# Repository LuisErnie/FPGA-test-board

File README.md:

# FPGA-test-board
FPGA Test Board designed for use with **DE10-NANO** by Terasic to provide external I/O devices to interface with the FPGA:
- 40 pin GPIO header split into 5 PMod ports
- 16x2 Character LCD
- 2 UART RS-485 ports
- 1 UART RS-282/USB port selected with switch
- 8 Optocoupled Outputs
- 8 ADC inputs 12-bit
- 8 DIP switch input

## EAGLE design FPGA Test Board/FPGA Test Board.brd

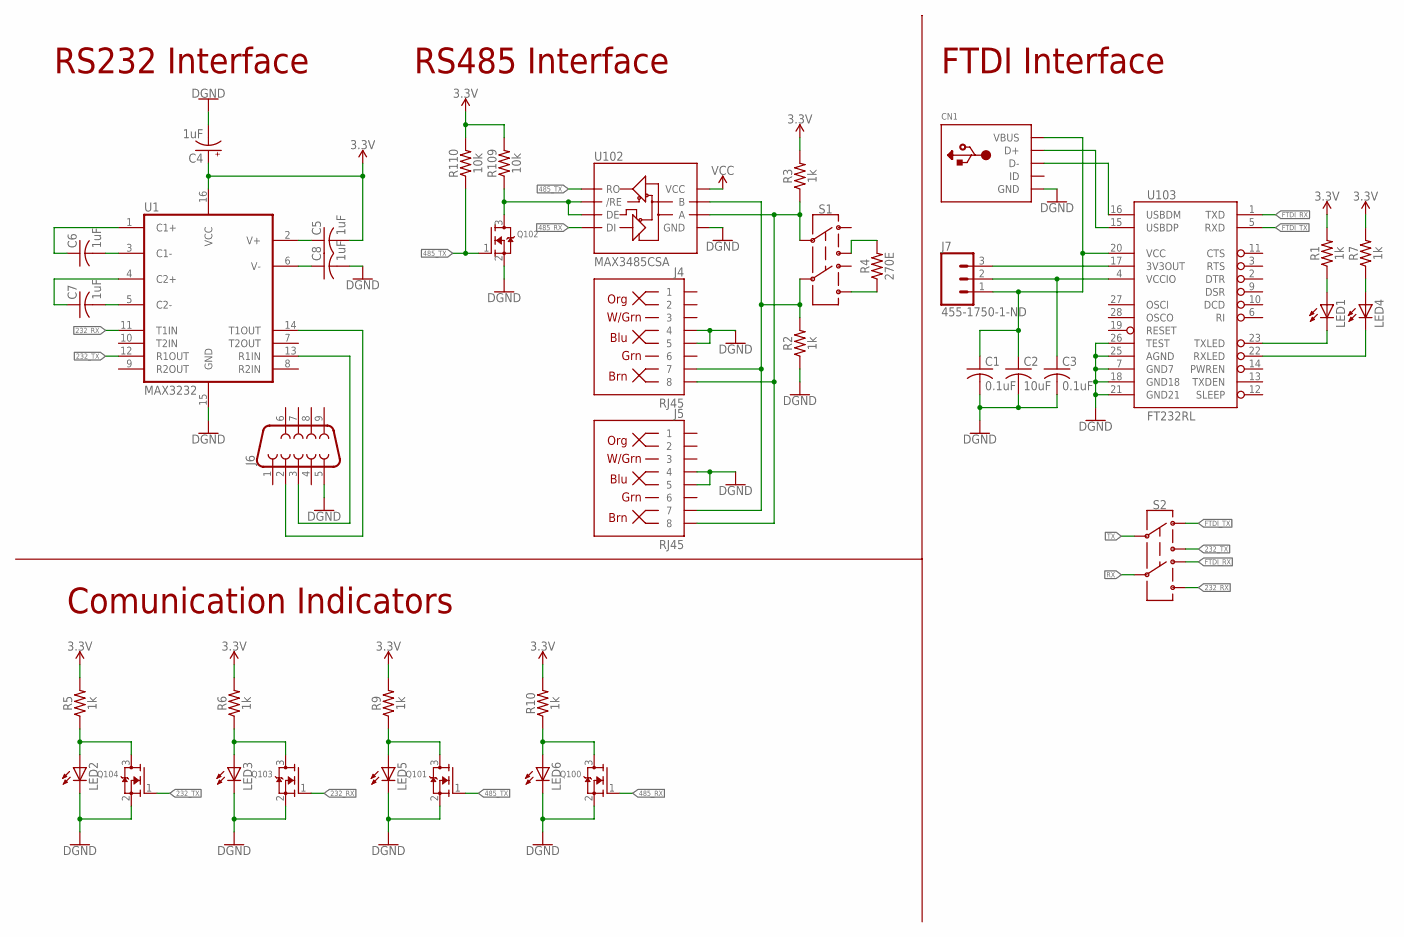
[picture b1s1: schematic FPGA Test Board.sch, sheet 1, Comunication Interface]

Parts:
C1, C3: 0.1uF; C0805
C2: 10uF; C0805
C4: 1uF; PANASONIC_B
C5, C6, C7, C8: 1uF; C0805
CN1: USBMINIB; USB-MINIB
J4, J5: RJ45; RJ45-8
J6: DB9FEMALE; DB9
J7: 455-1750-1-ND; 1X03
LED1, LED2, LED3, LED4, LED5, LED6: LEDCHIP-LED0805; CHIP-LED0805
Q100, Q101, Q102, Q103, Q104: MOSFET-NWAVE; SOT23-W
R1, R2, R3, R5, R6, R7, R9, R10: 1k; 0805
R4: 270E; 0805
R109, R110: 10k; 0805
S1, S2: SWITCH-DPDT-SMD-AYZ0202; SWITCH_DPDT_SMD_AYZ0202
U1: MAX3232; SO16
U102: MAX3485CSA; SO08
U103: FT232RL; SSOP28DB

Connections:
3.3V: C4.+, C5.2, R1.2, R3.2, R5.2, R6.2, R7.2, R9.2, R10.2, R109.2, R110.2, U1.16 (VCC); also elsewhere on the board
5V: U102.8 (VCC); also elsewhere on the board
232_RX: Q103.1 (G), S2.6, U1.11 (T1IN); also elsewhere on the board
232_TX: Q104.1 (G), S2.3, U1.12 (R1OUT); also elsewhere on the board
485_RX: Q100.1 (G), U102.4 (DI); also elsewhere on the board
485_TX: Q101.1 (G), Q102.1 (G), R110.1, U102.1 (RO); also elsewhere on the board
FTDI_RX: S2.4, U103.1 (TXD)
FTDI_TX: S2.1, U103.5 (RXD)
GND: C1.2, C2.2, C3.2, C4.-, C8.2, CN1.GND, J4.4, J4.5, J5.4, J5.5, J6.5, LED2.C, LED3.C, LED5.C, LED6.C, Q100.2 (S), Q101.2 (S), Q102.2 (S), Q103.2 (S), Q104.2 (S), R2.1, U1.15 (GND), U102.5 (GND), U103.7 (GND7), U103.18 (GND18), U103.21 (GND21), U103.25 (AGND), U103.26 (TEST); also elsewhere on the board
unnamed: C6.2, U1.3 (C1-)
unnamed: C5.1, U1.2 (V+)
unnamed: C6.1, U1.1 (C1+)
unnamed: C7.1, U1.4 (C2+)
unnamed: C7.2, U1.5 (C2-)
unnamed: C8.1, U1.6 (V-)
unnamed: J4.8, J5.8, R3.1, S1.2, U102.6 (A)
unnamed: LED3.A, Q103.3 (D), R6.1
unnamed: J6.2, U1.14 (T1OUT)
unnamed: J6.3, U1.13 (R1IN)
unnamed: LED5.A, Q101.3 (D), R9.1
unnamed: LED2.A, Q104.3 (D), R5.1
unnamed: LED6.A, Q100.3 (D), R10.1
unnamed: J4.7, J5.7, R2.2, S1.5, U102.7 (B)
unnamed: R4.1, S1.6
unnamed: Q102.3 (D), R109.1, U102.2 (/RE), U102.3 (DE)
unnamed: R4.2, S1.3
unnamed: C1.1, C2.1, CN1.VBUS, J7.1, U103.20 (VCC)
unnamed: LED1.A, R1.1
unnamed: LED1.C, U103.23 (TXLED)
unnamed: LED4.A, R7.1
unnamed: LED4.C, U103.22 (RXLED)
unnamed: CN1.D-, U103.16 (USBDM)
unnamed: CN1.D+, U103.15 (USBDP)
unnamed: J7.3, U103.17 (3V3OUT)
unnamed: C3.1, J7.2, U103.4 (VCCIO)
RX: S2.5
TX: S2.2

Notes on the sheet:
RS232 Interface
RS485 Interface
Comunication Indicators
FTDI Interface

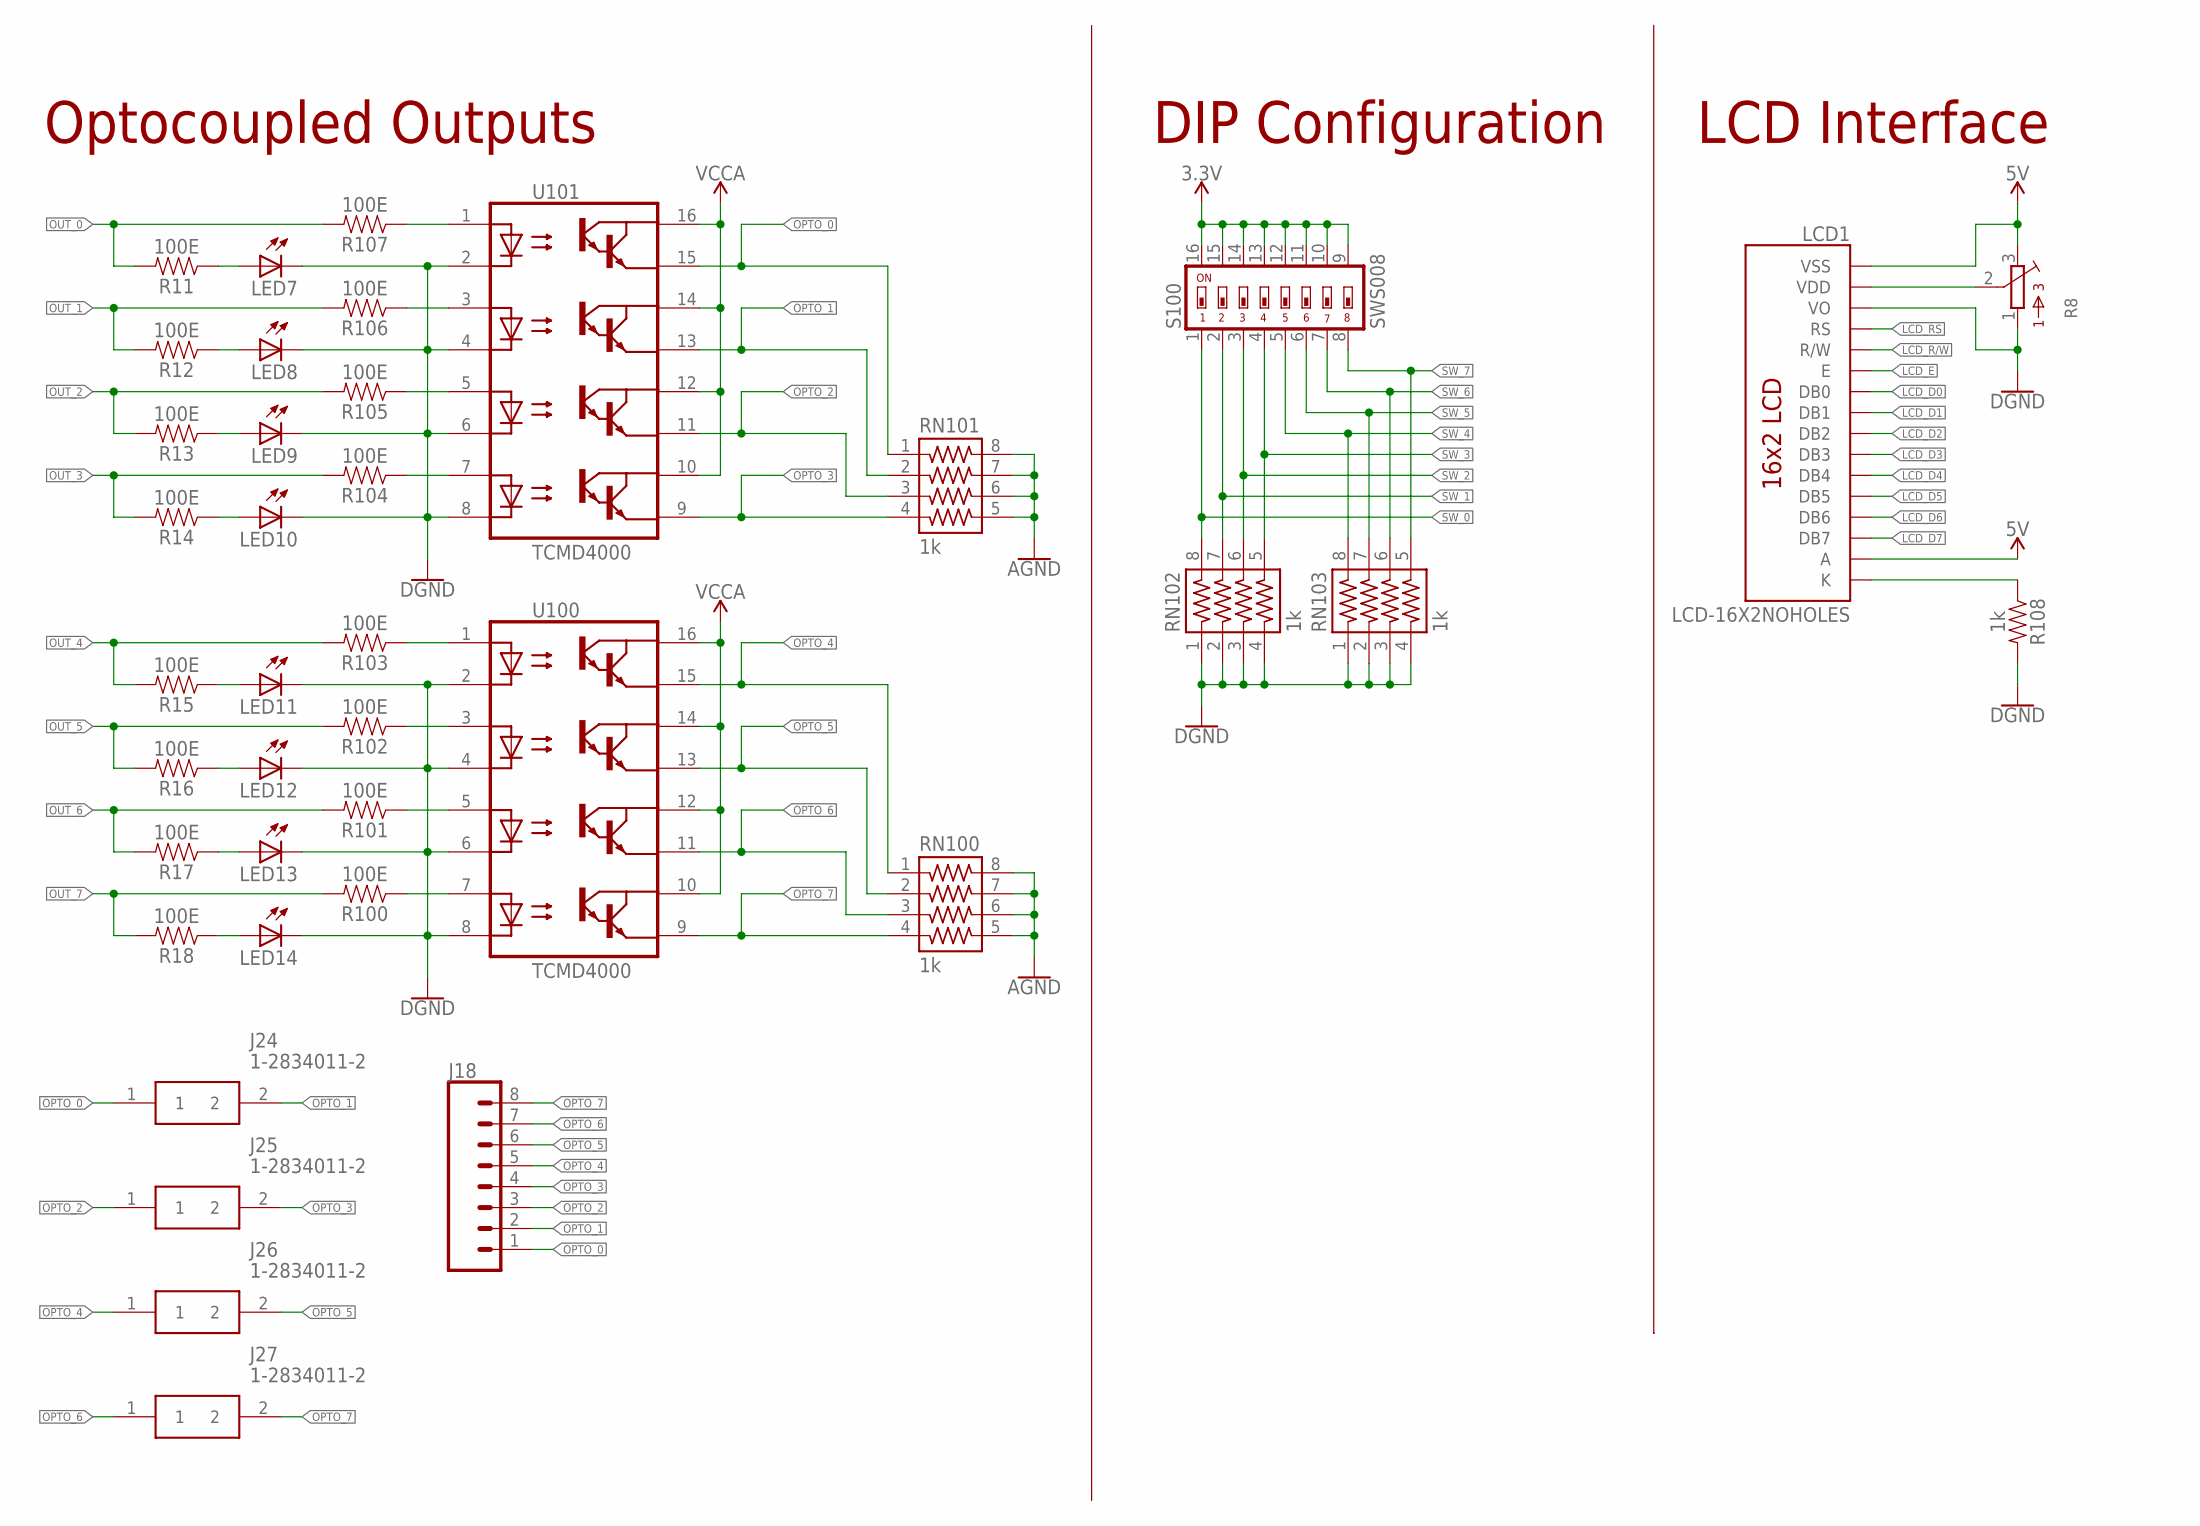
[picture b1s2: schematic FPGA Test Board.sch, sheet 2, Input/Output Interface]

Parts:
J18: CONN_08FEMALE_LOCK; 1X08_FEMALE_LOCK
J24, J25, J26, J27: 1-2834011-2; 128340112
LCD1: LCD-16X2NOHOLES; LCD-16X2_NOHOLESNOSILK
LED7, LED8, LED9, LED10, LED11, LED12, LED13, LED14: LEDCHIP-LED0805; CHIP-LED0805
R8: 3386-P; 3386P
R11, R12, R13, R14, R15, R16, R17, R18, R100, R101, R102, R103, R104, R105, R106, R107: 100E; 0805
R108: 1k; 0805
RN100, RN101, RN102, RN103: 1k; 743-8NS
S100: SWS008; SMS-008
U100, U101: TCMD4000; SOIC127P686X201-16N

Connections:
3.3V: S100.9, S100.10, S100.11, S100.12, S100.13, S100.14, S100.15, S100.16; also elsewhere on the board
5V: LCD1.1 (VSS), LCD1.15 (A), R8.3; also elsewhere on the board
AGND: RN100.5, RN100.6, RN100.7, RN100.8, RN101.5, RN101.6, RN101.7, RN101.8; also elsewhere on the board
GND: LCD1.3 (VO), LED7.C, LED8.C, LED9.C, LED10.C, LED11.C, LED12.C, LED13.C, LED14.C, R8.1, R108.2, RN102.1, RN102.2, RN102.3, RN102.4, RN103.1, RN103.2, RN103.3, RN103.4, U100.2 (C1), U100.4 (C2), U100.6 (C3), U100.8 (C4), U101.2 (C1), U101.4 (C2), U101.6 (C3), U101.8 (C4); also elsewhere on the board
LCD_D0: LCD1.7 (DB0); also elsewhere on the board
LCD_D1: LCD1.8 (DB1); also elsewhere on the board
LCD_D2: LCD1.9 (DB2); also elsewhere on the board
LCD_D3: LCD1.10 (DB3); also elsewhere on the board
LCD_D4: LCD1.11 (DB4); also elsewhere on the board
LCD_D5: LCD1.12 (DB5); also elsewhere on the board
LCD_D6: LCD1.13 (DB6); also elsewhere on the board
LCD_D7: LCD1.14 (DB7); also elsewhere on the board
LCD_E: LCD1.6 (E); also elsewhere on the board
LCD_R/W: LCD1.5 (R/W); also elsewhere on the board
LCD_RS: LCD1.4 (RS); also elsewhere on the board
unnamed: LCD1.2 (VDD), R8.2
unnamed: LCD1.16 (K), R108.1
unnamed: R107.1, U101.1 (A1)
unnamed: R106.1, U101.3 (A2)
unnamed: R105.1, U101.5 (A3)
unnamed: R104.1, U101.7 (A4)
unnamed: LED10.A, R14.1
unnamed: LED9.A, R13.1
unnamed: LED8.A, R12.1
unnamed: LED7.A, R11.1
unnamed: R103.1, U100.1 (A1)
unnamed: R102.1, U100.3 (A2)
unnamed: R101.1, U100.5 (A3)
unnamed: R100.1, U100.7 (A4)
unnamed: LED14.A, R18.1
unnamed: LED13.A, R17.1
unnamed: LED12.A, R16.1
unnamed: LED11.A, R15.1
OPTO_0: J18.1, J24.1, RN101.1, U101.15 (E1)
OPTO_1: J18.2, J24.2, RN101.2, U101.13 (E2)
OPTO_2: J18.3, J25.1, RN101.3, U101.11 (E3)
OPTO_3: J18.4, J25.2, RN101.4, U101.9 (E4)
OPTO_4: J18.5, J26.1, RN100.1, U100.15 (E1)
OPTO_5: J18.6, J26.2, RN100.2, U100.13 (E2)
OPTO_6: J18.7, J27.1, RN100.3, U100.11 (E3)
OPTO_7: J18.8, J27.2, RN100.4, U100.9 (E4)
OUT_0: R11.2, R107.2; also elsewhere on the board
OUT_1: R12.2, R106.2; also elsewhere on the board
OUT_2: R13.2, R105.2; also elsewhere on the board
OUT_3: R14.2, R104.2; also elsewhere on the board
OUT_4: R15.2, R103.2; also elsewhere on the board
OUT_5: R16.2, R102.2; also elsewhere on the board
OUT_6: R17.2, R101.2; also elsewhere on the board
OUT_7: R18.2, R100.2; also elsewhere on the board
SW_0: RN102.8, S100.1; also elsewhere on the board
SW_1: RN102.7, S100.2; also elsewhere on the board
SW_2: RN102.6, S100.3; also elsewhere on the board
SW_3: RN102.5, S100.4; also elsewhere on the board
SW_4: RN103.8, S100.5; also elsewhere on the board
SW_5: RN103.7, S100.6; also elsewhere on the board
SW_6: RN103.6, S100.7; also elsewhere on the board
SW_7: RN103.5, S100.8; also elsewhere on the board
VCCA: U100.10 (CO4), U100.12 (CO3), U100.14 (CO2), U100.16 (CO1), U101.10 (CO4), U101.12 (CO3), U101.14 (CO2), U101.16 (CO1); also elsewhere on the board

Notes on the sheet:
Optocoupled Outputs
DIP Configuration
LCD Interface

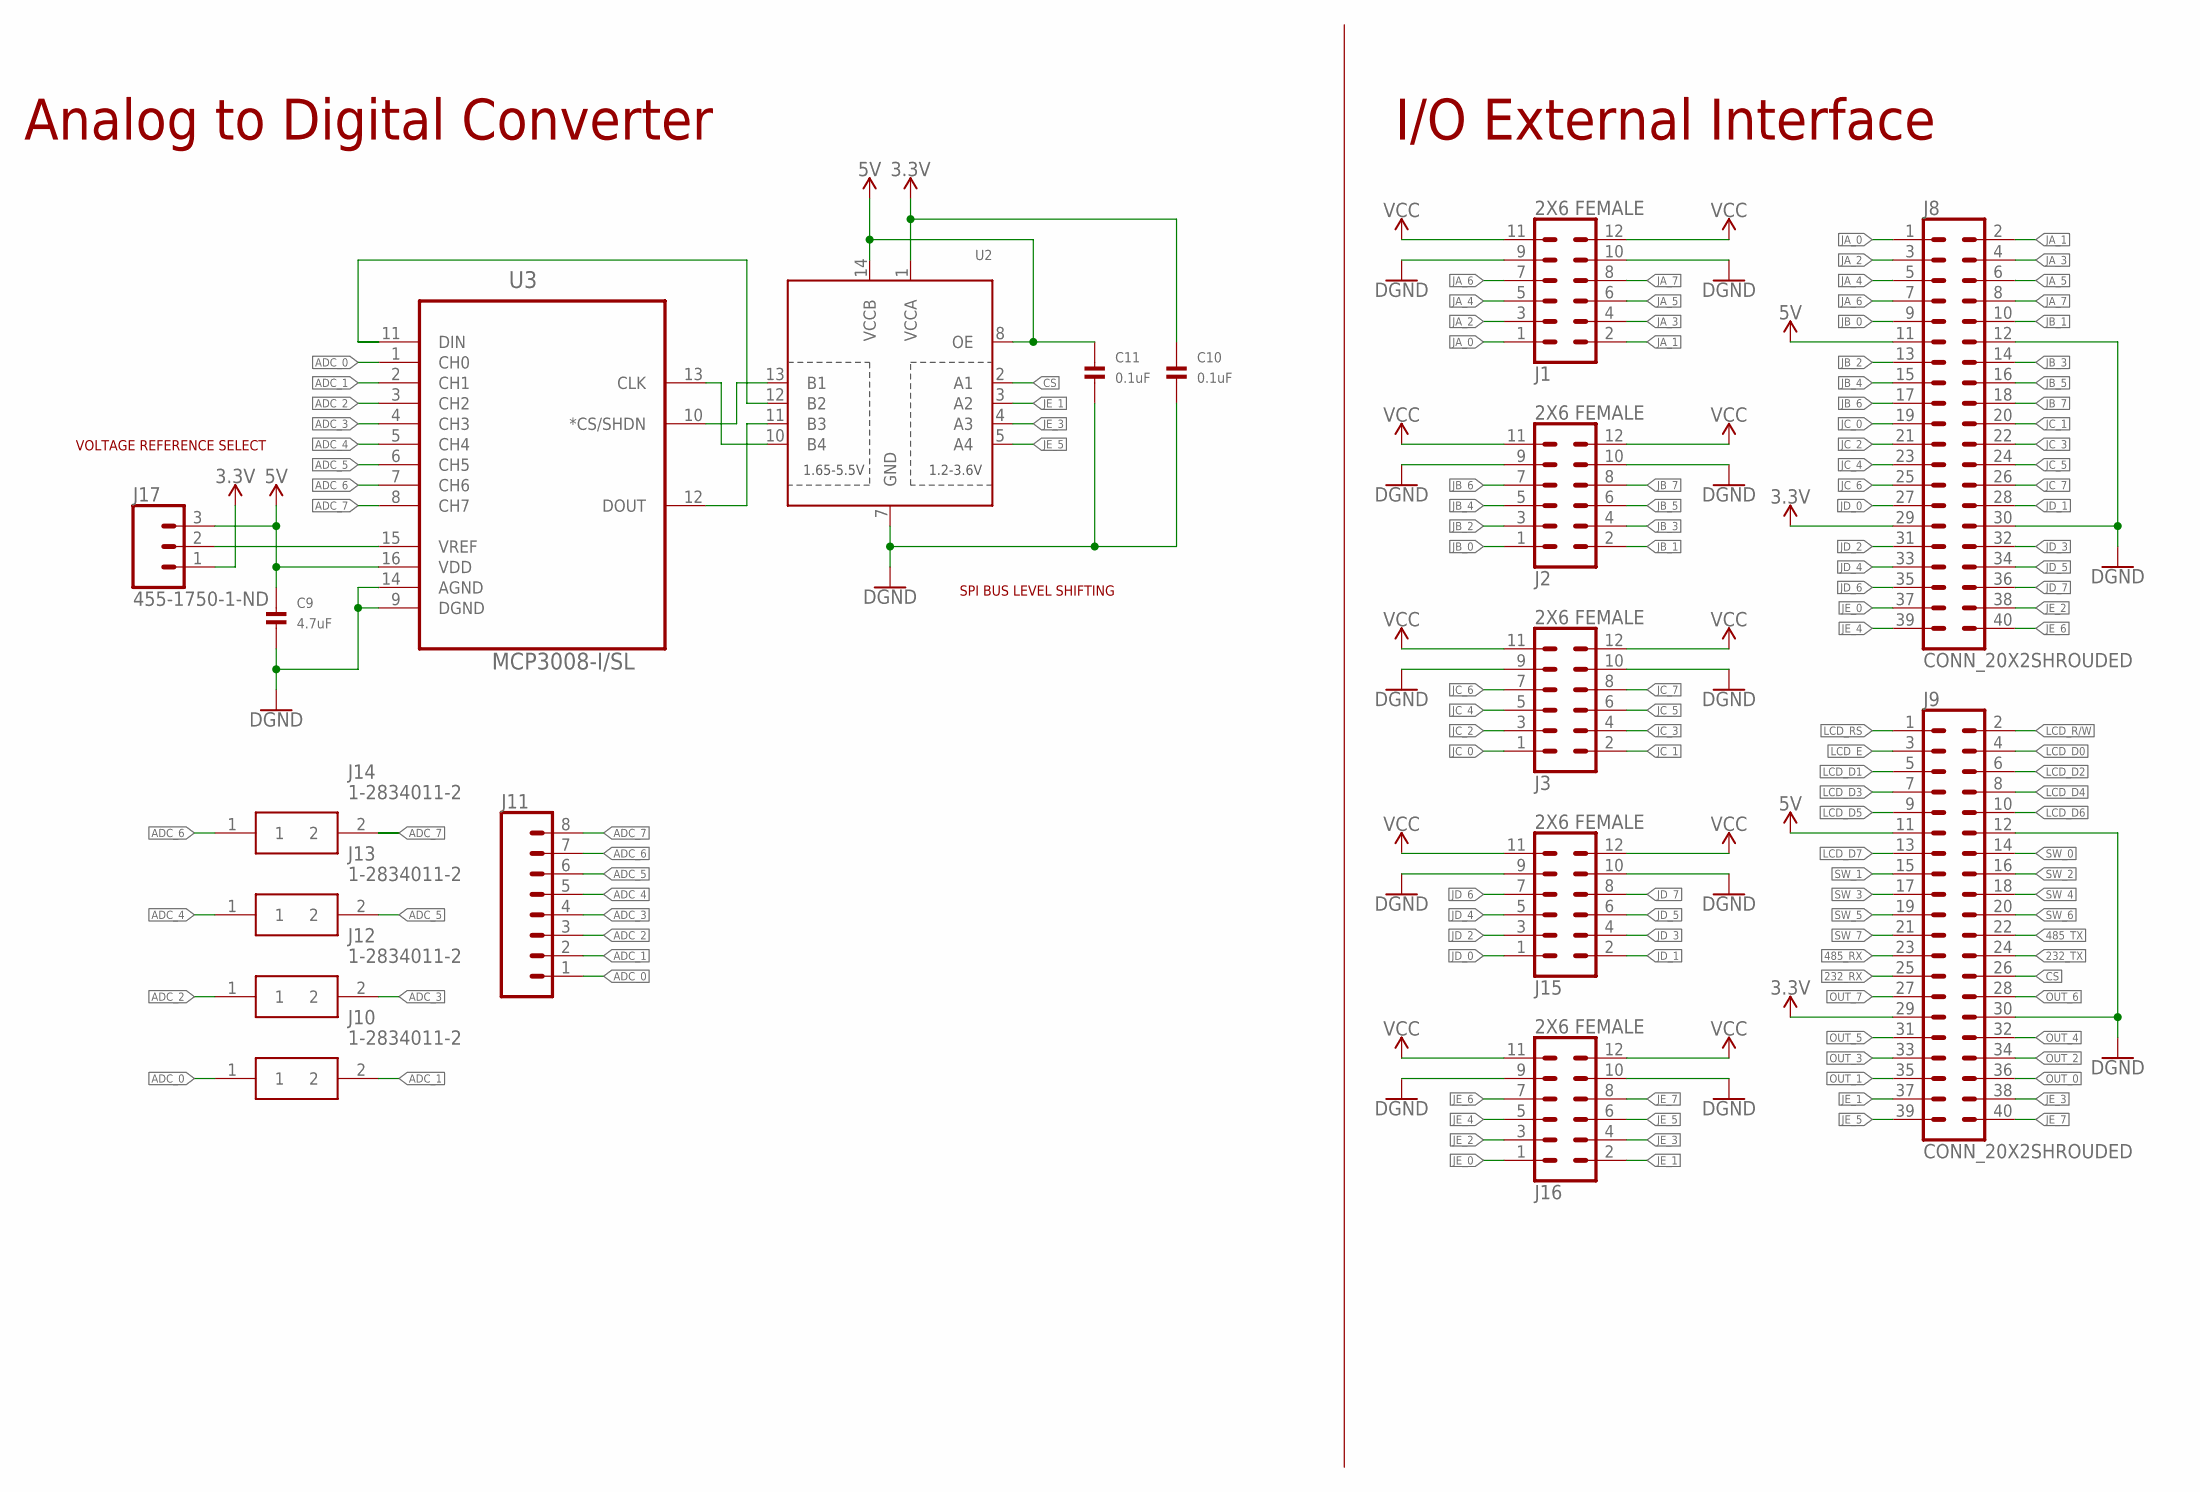
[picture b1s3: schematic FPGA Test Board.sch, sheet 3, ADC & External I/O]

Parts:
C9: 4.7uF; 0805_NOTHERMALS
C10, C11: 0.1uF; 0805_NOTHERMALS
J1, J2, J3, J15, J16: 2X6 FEMALE; 2X6
J8, J9: CONN_20X2SHROUDED; 2X20_SHROUDED
J10, J12, J13, J14: 1-2834011-2; 128340112
J11: CONN_08FEMALE_LOCK; 1X08_FEMALE_LOCK
J17: 455-1750-1-ND; 1X03
U2: TXB0104PWR; TSSOP14
U3: MCP3008-I/SL; SOIC127P600X175-16N

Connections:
3.3V: C10.1, J8.29, J9.29, J17.1, U2.1 (VCCA); also elsewhere on the board
5V: C9.1, C11.1, J8.11, J9.11, J17.3, U2.8 (OE), U2.14 (VCCB), U3.16 (VDD); also elsewhere on the board
232_RX: J9.25; also elsewhere on the board
232_TX: J9.24; also elsewhere on the board
485_RX: J9.23; also elsewhere on the board
485_TX: J9.22; also elsewhere on the board
ADC_0: J10.1, J11.1, U3.1 (CH0)
ADC_1: J10.2, J11.2, U3.2 (CH1)
ADC_2: J11.3, J12.1, U3.3 (CH2)
ADC_3: J11.4, J12.2, U3.4 (CH3)
ADC_4: J11.5, J13.1, U3.5 (CH4)
ADC_5: J11.6, J13.2, U3.6 (CH5)
ADC_6: J11.7, J14.1, U3.7 (CH6)
ADC_7: J11.8, J14.2, U3.8 (CH7)
CS: J9.26, U2.2 (A1)
GND: C9.2, C10.2, C11.2, J1.9, J1.10, J2.9, J2.10, J3.9, J3.10, J8.12, J8.30, J9.12, J9.30, J15.9, J15.10, J16.9, J16.10, U2.7 (GND), U3.9 (DGND), U3.14 (AGND); also elsewhere on the board
JA_0: J1.1, J8.1
JA_1: J1.2, J8.2
JA_2: J1.3, J8.3
JA_3: J1.4, J8.4
JA_4: J1.5, J8.5
JA_5: J1.6, J8.6
JA_6: J1.7, J8.7
JA_7: J1.8, J8.8
JB_0: J2.1, J8.9
JB_1: J2.2, J8.10
JB_2: J2.3, J8.13
JB_3: J2.4, J8.14
JB_4: J2.5, J8.15
JB_5: J2.6, J8.16
JB_6: J2.7, J8.17
JB_7: J2.8, J8.18
JC_0: J3.1, J8.19
JC_1: J3.2, J8.20
JC_2: J3.3, J8.21
JC_3: J3.4, J8.22
JC_4: J3.5, J8.23
JC_5: J3.6, J8.24
JC_6: J3.7, J8.25
JC_7: J3.8, J8.26
JD_0: J8.27, J15.1
JD_1: J8.28, J15.2
JD_2: J8.31, J15.3
JD_3: J8.32, J15.4
JD_4: J8.33, J15.5
JD_5: J8.34, J15.6
JD_6: J8.35, J15.7
JD_7: J8.36, J15.8
JE_0: J8.37, J16.1
JE_1: J9.37, J16.2, U2.3 (A2)
JE_2: J8.38, J16.3
JE_3: J9.38, J16.4, U2.4 (A3)
JE_4: J8.39, J16.5
JE_5: J9.39, J16.6, U2.5 (A4)
JE_6: J8.40, J16.7
JE_7: J9.40, J16.8
LCD_D0: J9.4; also elsewhere on the board
LCD_D1: J9.5; also elsewhere on the board
LCD_D2: J9.6; also elsewhere on the board
LCD_D3: J9.7; also elsewhere on the board
LCD_D4: J9.8; also elsewhere on the board
LCD_D5: J9.9; also elsewhere on the board
LCD_D6: J9.10; also elsewhere on the board
LCD_D7: J9.13; also elsewhere on the board
LCD_E: J9.3; also elsewhere on the board
LCD_R/W: J9.2; also elsewhere on the board
LCD_RS: J9.1; also elsewhere on the board
unnamed: U2.13 (B1), U3.10 (*CS/SHDN)
unnamed: U2.10 (B4), U3.13 (CLK)
unnamed: U2.11 (B3), U3.12 (DOUT)
unnamed: U2.12 (B2), U3.11 (DIN)
unnamed: J17.2, U3.15 (VREF)
OUT_0: J9.36; also elsewhere on the board
OUT_1: J9.35; also elsewhere on the board
OUT_2: J9.34; also elsewhere on the board
OUT_3: J9.33; also elsewhere on the board
OUT_4: J9.32; also elsewhere on the board
OUT_5: J9.31; also elsewhere on the board
OUT_6: J9.28; also elsewhere on the board
OUT_7: J9.27; also elsewhere on the board
SW_0: J9.14; also elsewhere on the board
SW_1: J9.15; also elsewhere on the board
SW_2: J9.16; also elsewhere on the board
SW_3: J9.17; also elsewhere on the board
SW_4: J9.18; also elsewhere on the board
SW_5: J9.19; also elsewhere on the board
SW_6: J9.20; also elsewhere on the board
SW_7: J9.21; also elsewhere on the board
VCC: J1.11, J1.12, J2.11, J2.12, J3.11, J3.12, J15.11, J15.12, J16.11, J16.12; also elsewhere on the board

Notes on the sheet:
VOLTAGE REFERENCE SELECT
SPI BUS LEVEL SHIFTING
Analog to Digital Converter
I/O External Interface

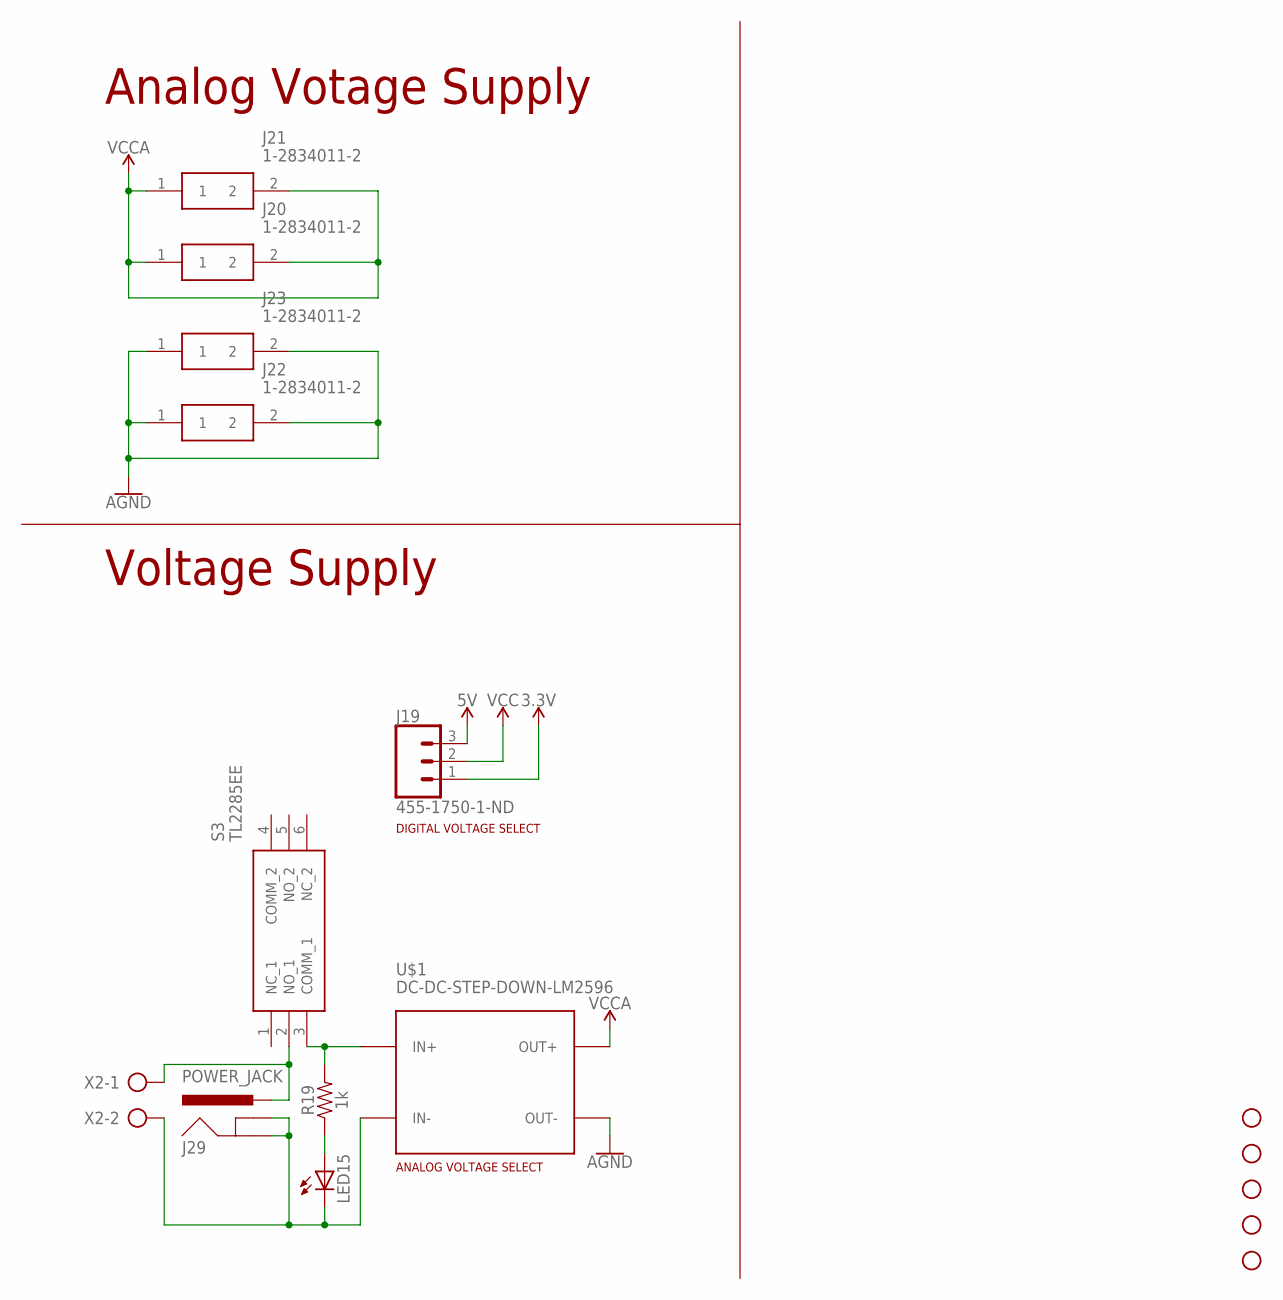
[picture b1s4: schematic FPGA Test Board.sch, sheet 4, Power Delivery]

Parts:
H1, H5, H6, H7, H8: STAND-OFF
J19: 455-1750-1-ND; 1X03
J20, J21, J22, J23: 1-2834011-2; 128340112
J29: POWER_JACK; POWER_JACK_PTH
LED15: LEDCHIP-LED0805; CHIP-LED0805
R19: 1k; 0805
S3: TL2285EE
U$1: DC-DC-STEP-DOWN-LM2596
X2: AK500/2-H

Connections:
3.3V: J19.1; also elsewhere on the board
5V: J19.3; also elsewhere on the board
AGND: J22.1, J22.2, J23.1, J23.2, U$1.OUT-; also elsewhere on the board
unnamed: R19.2, S3.3 (COMM_1), U$1.IN+
unnamed: LED15.A, R19.1
unnamed: J29.PWR, S3.2 (NO_1), X2.1
unnamed: J29.GND, J29.GNDBREAK, LED15.C, U$1.IN-, X2.2
VCC: J19.2; also elsewhere on the board
VCCA: J20.1, J20.2, J21.1, J21.2, U$1.OUT+; also elsewhere on the board

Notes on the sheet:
DIGITAL VOLTAGE SELECT
ANALOG VOLTAGE SELECT
Analog Votage Supply
Voltage Supply

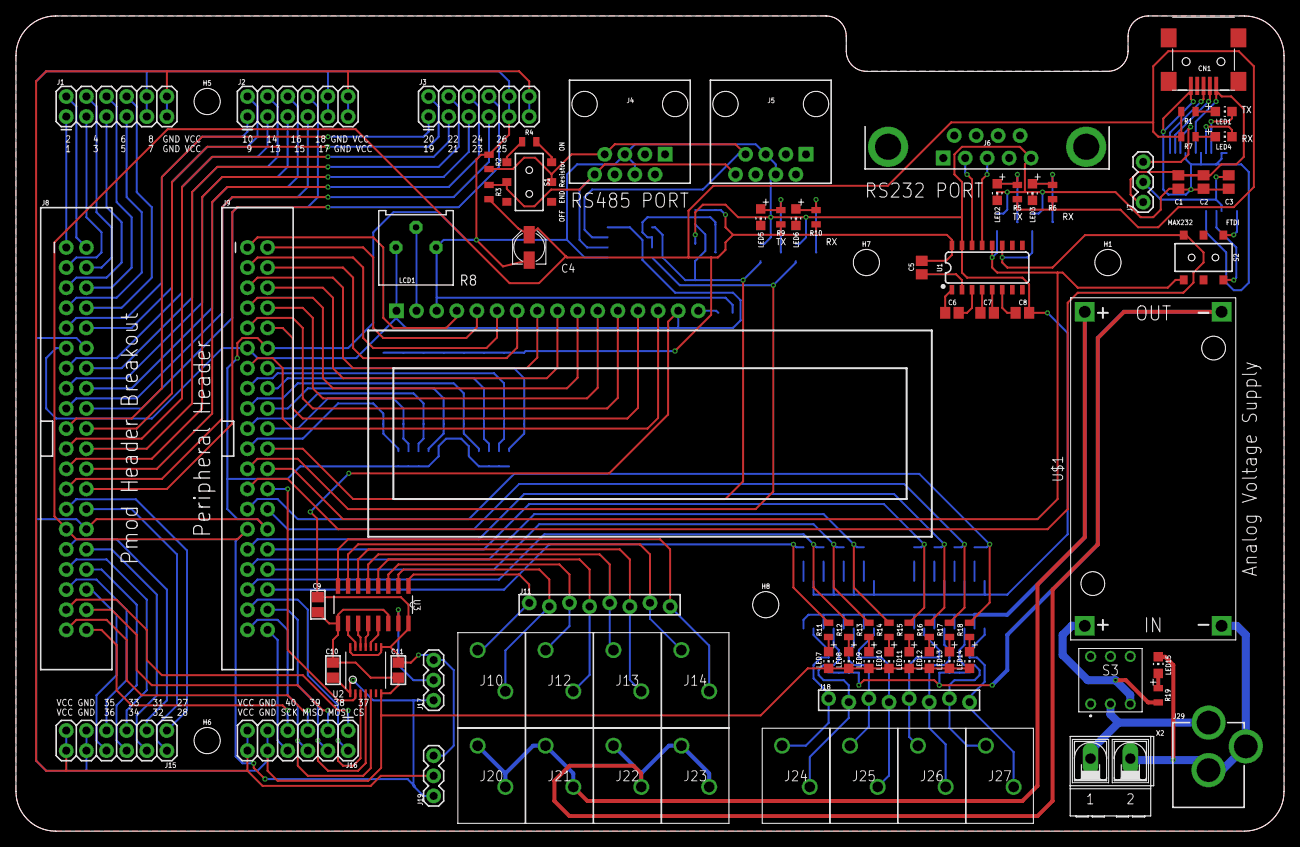
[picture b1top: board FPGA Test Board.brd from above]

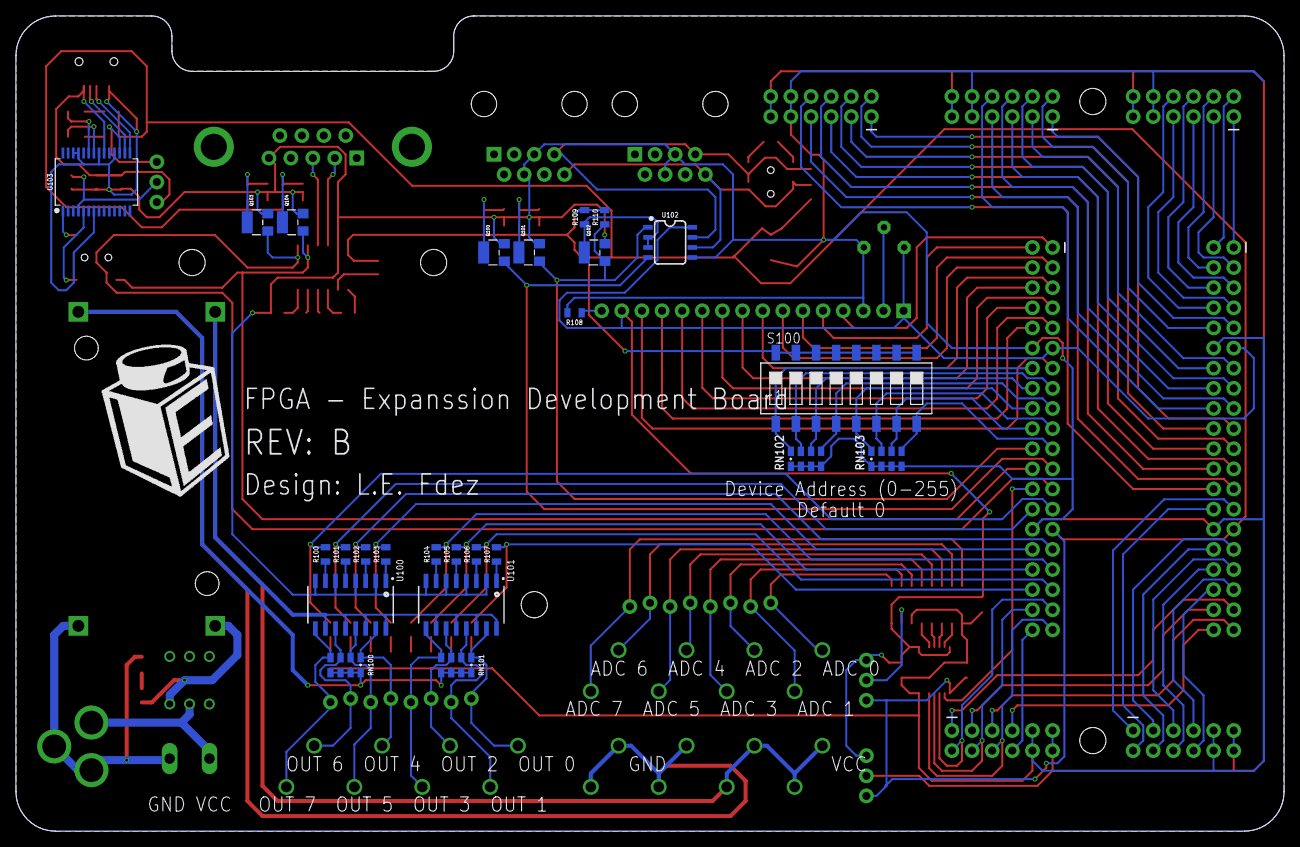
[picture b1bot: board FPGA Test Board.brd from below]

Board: 2 copper layers, 160.0 x 102.9 mm, 113 parts (25 on the bottom side), 149 nets.

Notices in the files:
parts and their libraries:
microbuilder: This work is placed in the public domain, and may be freely used for commercial and non-commercial work with the following conditions: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
SparkFun-Connectors: Licensing: Creative Commons ShareAlike 4.0 International - https://creativecommons.org/licenses/by-sa/4.0
